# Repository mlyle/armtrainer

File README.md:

# ARM Trainer

This is a minimal monitor and and hardware stack for a small microcontroller trainer board, that was used to teach a Computer Organization class to students from ages 11-14.

Microprocessor trainers were a commonplace tool used to learn computing in the 1970s and early 1980s.  They replicated the console found on minicomputers, and allowed engineers to gain experience writing programs in machine code.

The Computer Organization class that I taught was a "how computers work" class with minimal use of conventional computers in the classroom.  We focused initially on gates, building from there to understand simple combinatorial and sequential circuits, and eventually ALUs, register files, and microprocessor subsystems.  This culminated in a study of ARM-Thumb machine code.

ARM-Thumb machine code was a fairly ideal architecture for students to learn, because:

* It is a real architecture, in real use.
* It has a reasonable number of general purpose registers.
* A fixed-length, relatively simple encoding avoids unnecessary complexity.

## Repository Layout

* `src/` and `inc/` contain the trainer firmware.
* `hw/` contains the KiCad hardware designs and manufacturing outputs.
* `arm-manual/` contains the student manual sources.
* `examples/` contains programs captured from trainers during class.
* `tools/` contains host-side conversion, disassembly, capture, and printing tools.

Run `make tools` to build the host-side utilities in `build/tools/`. The classroom
scripts should be run from any directory; they locate the repository and examples
automatically.

## Example Program

By a student, Robin K:

    20000000	DF20		(clear screen)
    20000002	2001		(mov r0, #1)
    20000004	2102		(mov r1, #1)
    20000006	180A		(add r2, r0, r1)
    20000008	DF21		(print contents of register 0)
    2000000A	4608		(mov r0, r1)
    2000000C	4611		(mov r1, r2)
    2000000E	E7FA		(b 20000006)

## TODO

* Students have complained that some invalid instructions-- BBAD, EF78-- seem to lock up the machine monitor.  I think I removed some safeguard code that I didn't think was necessary, but I need to inspect that again.
* Input calls do not allow the user to enter the number "0".
* The manual should be updated with some of the system calls that have not been documented
  * Branch calculation formulae are wrong in the manual.
  * In particular, the input calls.
  * There may be a typo in the subtract register instruction.
  * The display icon and screen coordinate system could be more clearly explained
  * Need to update manual for new key shortcuts
* Overall curriculum, etc, should get posted here.

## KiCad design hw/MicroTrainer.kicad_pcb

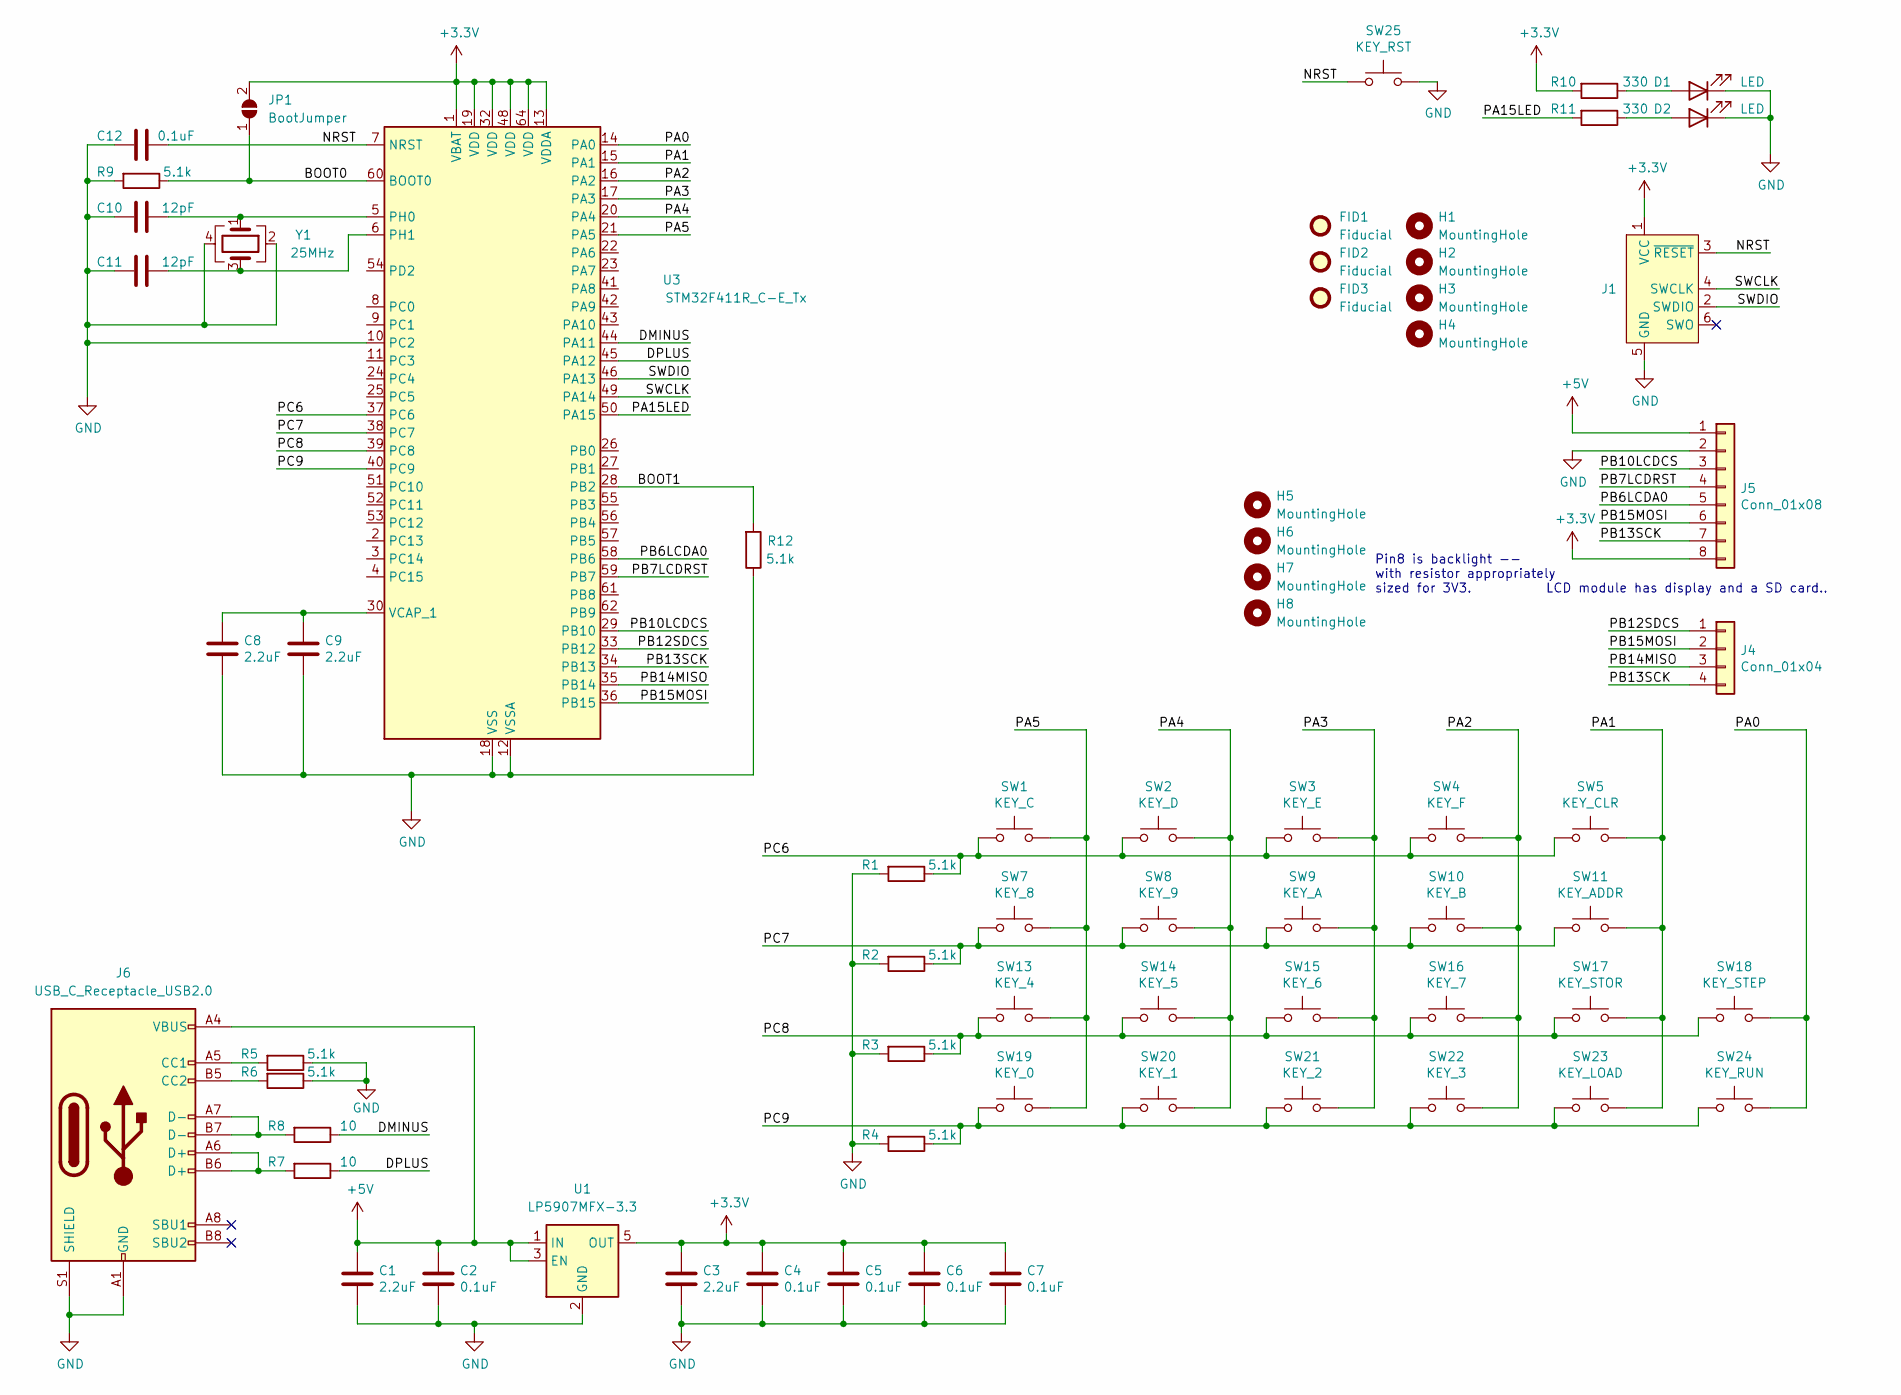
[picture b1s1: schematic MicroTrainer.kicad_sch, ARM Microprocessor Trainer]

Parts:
C1, C3, C8, C9: 2.2uF; C_0603_1608Metric; LCSC C23630
C2, C4, C5, C6, C7, C12: 0.1uF; C_0603_1608Metric; LCSC C14663
C10, C11: 12pF; C_0603_1608Metric; LCSC C38523
D1, D2: LED; LED_0805_2012Metric; LCSC C2297
FID1, FID2, FID3: Fiducial; Fiducial_1mm_Mask2mm
H1, H2, H3, H4, H5, H6, H7, H8: MountingHole; MountingHole_3.2mm_M3
J1: Conn_ARM_SWD_TagConnect_TC2030; Tag-Connect_TC2030-IDC-FP_2x03_P1.27mm_Vertical
J4: Conn_01x04; PinSocket_1x04_P2.54mm_Vertical
J5: Conn_01x08; PinSocket_1x08_P2.54mm_Vertical
J6: USB_C_Receptacle_USB2.0; USB_C_Receptacle_G-Switch_GT-USB-7010ASV; LCSC C2988369
JP1: BootJumper; SolderJumper-2_P1.3mm_Open_RoundedPad1.0x1.5mm
R1, R2, R3, R4, R5, R6, R9, R12: 5.1k; R_0603_1608Metric; LCSC C23186
R7, R8: 10; R_0603_1608Metric; LCSC C22859
R10, R11: 330; R_0603_1608Metric; LCSC C23138
SW1: KEY_C; SW_Cherry_MX_1.00u_PCB
SW2: KEY_D; SW_Cherry_MX_1.00u_PCB
SW3: KEY_E; SW_Cherry_MX_1.00u_PCB
SW4: KEY_F; SW_Cherry_MX_1.00u_PCB
SW5: KEY_CLR; SW_Cherry_MX_1.00u_PCB
SW7: KEY_8; SW_Cherry_MX_1.00u_PCB
SW8: KEY_9; SW_Cherry_MX_1.00u_PCB
SW9: KEY_A; SW_Cherry_MX_1.00u_PCB
SW10: KEY_B; SW_Cherry_MX_1.00u_PCB
SW11: KEY_ADDR; SW_Cherry_MX_1.00u_PCB
SW13: KEY_4; SW_Cherry_MX_1.00u_PCB
SW14: KEY_5; SW_Cherry_MX_1.00u_PCB
SW15: KEY_6; SW_Cherry_MX_1.00u_PCB
SW16: KEY_7; SW_Cherry_MX_1.00u_PCB
SW17: KEY_STOR; SW_Cherry_MX_1.00u_PCB
SW18: KEY_STEP; SW_Cherry_MX_1.00u_PCB
SW19: KEY_0; SW_Cherry_MX_1.00u_PCB
SW20: KEY_1; SW_Cherry_MX_1.00u_PCB
SW21: KEY_2; SW_Cherry_MX_1.00u_PCB
SW22: KEY_3; SW_Cherry_MX_1.00u_PCB
SW23: KEY_LOAD; SW_Cherry_MX_1.00u_PCB
SW24: KEY_RUN; SW_Cherry_MX_1.00u_PCB
SW25: KEY_RST; SW_Cherry_MX_1.00u_PCB
U1: LP5907MFX-3.3; SOT-23-5; LCSC C80670
U3: STM32F411R_C-E_Tx; LQFP-64_10x10mm_P0.5mm; LCSC C89374
Y1: 25MHz; Crystal_SMD_3225-4Pin_3.2x2.5mm; LCSC C9006

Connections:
+3V3: C3.1, C4.1, C5.1, C6.1, C7.1, J1.1 (VCC), J5.8, JP1.2 (B), R10.2, U1.5 (OUT), U3.1 (VBAT), U3.13 (VDDA), U3.19 (VDD), U3.32 (VDD), U3.48 (VDD), U3.64 (VDD)
+5V: C1.1, C2.1, J5.1, J6.A4 (VBUS), J6.A9 (VBUS), J6.B4 (VBUS), J6.B9 (VBUS), U1.1 (IN), U1.3 (EN)
/BOOT0: JP1.1 (A), R9.1, U3.60 (BOOT0)
/BOOT1: R12.2, U3.28 (PB2)
/DMINUS: R8.1, U3.44 (PA11)
/DPLUS: R7.1, U3.45 (PA12)
/NRST: C12.2, J1.3 (~RESET), SW25.1, U3.7 (NRST)
/PA0: SW18.2, SW24.2, U3.14 (PA0)
/PA1: SW5.2, SW11.2, SW17.2, SW23.2, U3.15 (PA1)
/PA2: SW4.2, SW10.2, SW16.2, SW22.2, U3.16 (PA2)
/PA3: SW3.2, SW9.2, SW15.2, SW21.2, U3.17 (PA3)
/PA4: SW2.2, SW8.2, SW14.2, SW20.2, U3.20 (PA4)
/PA5: SW1.2, SW7.2, SW13.2, SW19.2, U3.21 (PA5)
/PA15LED: R11.2, U3.50 (PA15)
/PB6LCDA0: J5.5, U3.58 (PB6)
/PB7LCDRST: J5.4, U3.59 (PB7)
/PB10LCDCS: J5.3, U3.29 (PB10)
/PB12SDCS: J4.1, U3.33 (PB12)
/PB13SCK: J4.4, J5.7, U3.34 (PB13)
/PB14MISO: J4.3, U3.35 (PB14)
/PB15MOSI: J4.2, J5.6, U3.36 (PB15)
/PC6: R1.1, SW1.1, SW2.1, SW3.1, SW4.1, SW5.1, U3.37 (PC6)
/PC7: R2.1, SW7.1, SW8.1, SW9.1, SW10.1, SW11.1, U3.38 (PC7)
/PC8: R3.1, SW13.1, SW14.1, SW15.1, SW16.1, SW17.1, SW18.1, U3.39 (PC8)
/PC9: R4.1, SW19.1, SW20.1, SW21.1, SW22.1, SW23.1, SW24.1, U3.40 (PC9)
/SWCLK: J1.4 (SWCLK), U3.49 (PA14)
/SWDIO: J1.2 (SWDIO), U3.46 (PA13)
GND: C1.2, C2.2, C3.2, C4.2, C5.2, C6.2, C7.2, C8.2, C9.2, C10.1, C11.1, C12.1, D1.1 (K), D2.1 (K), J1.5 (GND), J5.2, J6.A1 (GND), J6.A12 (GND), J6.B1 (GND), J6.B12 (GND), J6.S1 (SHIELD), R1.2, R2.2, R3.2, R4.2, R5.1, R6.1, R9.2, R12.1, SW25.2, U1.2 (GND), U3.10 (PC2), U3.12 (VSSA), U3.18 (VSS), U3.31 (VSS), U3.47 (VSS), U3.63 (VSS), Y1.2, Y1.4
unnamed: D1.2 (A), R10.1
unnamed: D2.2 (A), R11.1
unnamed: J6.A5 (CC1), R5.2
unnamed: J6.B5 (CC2), R6.2
unnamed: J6.A6 (D+), J6.B6 (D+), R7.2
unnamed: J6.A7 (D-), J6.B7 (D-), R8.2
unnamed: C10.2, U3.5 (PH0), Y1.1
unnamed: C11.2, U3.6 (PH1), Y1.3
unnamed: C8.1, C9.1, U3.30 (VCAP_1)

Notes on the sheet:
LCD module has display and a SD card..
Pin8 is backlight -- with resistor appropriately sized for 3V3.

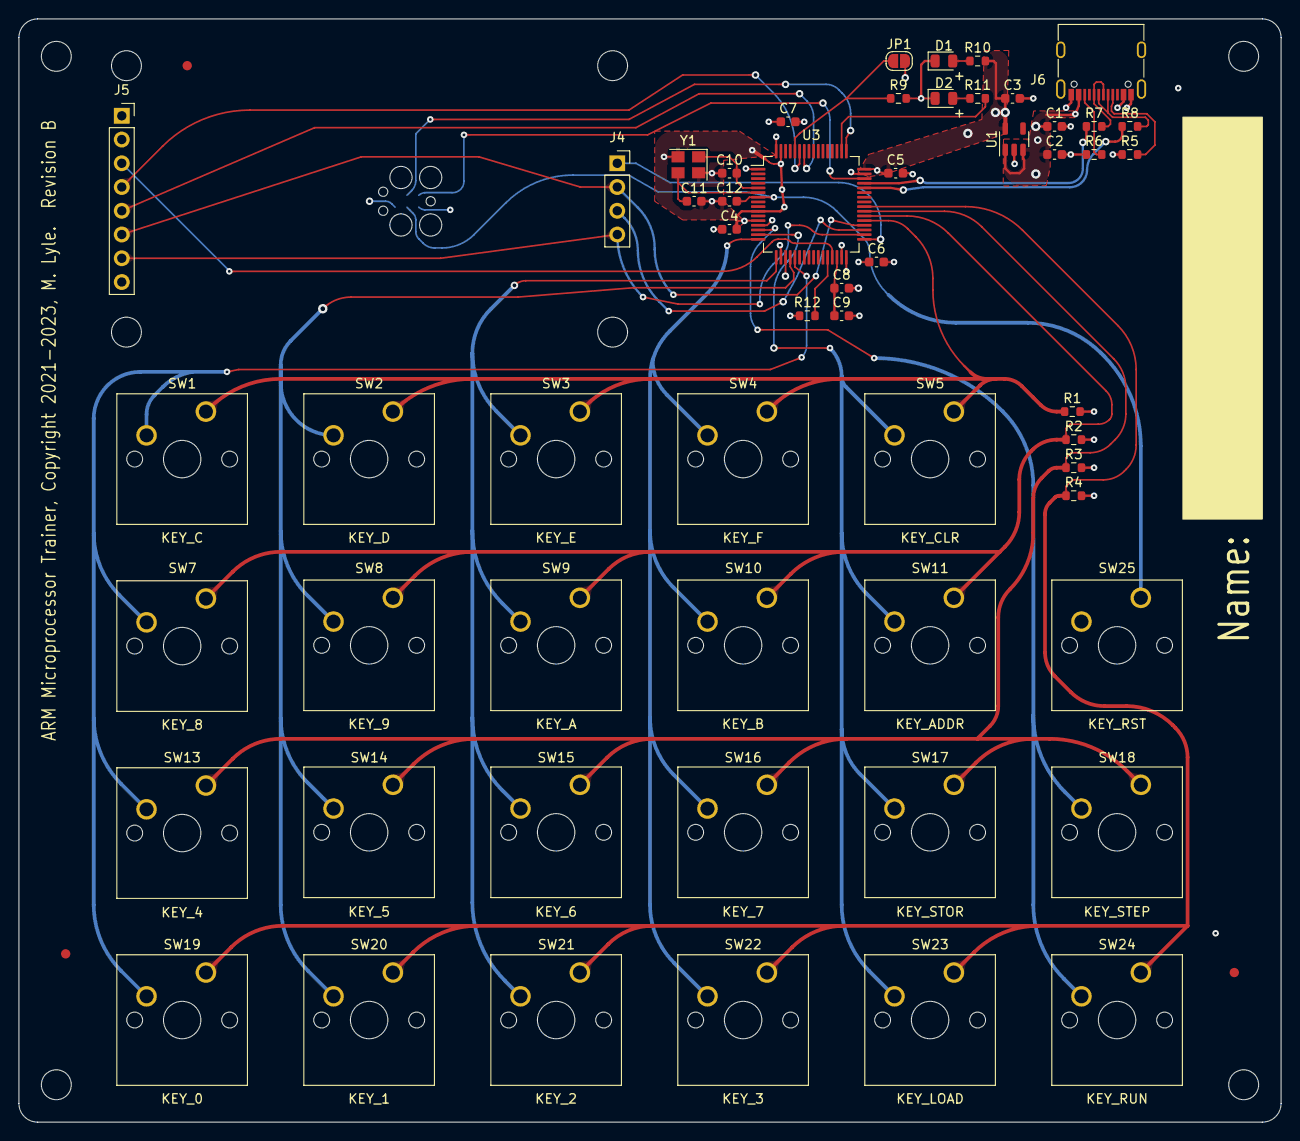
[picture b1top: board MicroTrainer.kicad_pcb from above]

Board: 4 copper layers, 135.0 x 118.0 mm, 68 parts (1 on the bottom side), 37 nets.

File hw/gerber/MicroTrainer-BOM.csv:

Comment,Designator,Footprint,LCSC
"2.2uF","C1,C3,C8,C9","Capacitor_SMD:C_0603_1608Metric","C23630"
"12pF","C10,C11","Capacitor_SMD:C_0603_1608Metric","C38523"
"0.1uF","C2,C4,C5,C6,C7,C12","Capacitor_SMD:C_0603_1608Metric","C14663"
"LED","D1,D2","LED_SMD:LED_0805_2012Metric","C2297"
"Fiducial","FID1,FID2,FID3","Fiducial:Fiducial_1mm_Mask2mm",""
"MountingHole","H1,H2,H3,H4,H5,H6,H7,H8","MountingHole:MountingHole_3.2mm_M3",""
"Conn_01x04","J4","Connector_PinSocket_2.54mm:PinSocket_1x04_P2.54mm_Vertical",""
"Conn_01x08","J5","Connector_PinSocket_2.54mm:PinSocket_1x08_P2.54mm_Vertical",""
"USB_C_Receptacle_USB2.0","J6","Connector_USB:USB_C_Receptacle_G-Switch_GT-USB-7010ASV","C2988369"
"BootJumper","JP1","Jumper:SolderJumper-2_P1.3mm_Open_RoundedPad1.0x1.5mm",""
"5.1k","R1,R2,R3,R4,R5,R6,R9,R12","Resistor_SMD:R_0603_1608Metric","C23186"
"330","R10,R11","Resistor_SMD:R_0603_1608Metric","C23138"
"10","R7,R8","Resistor_SMD:R_0603_1608Metric","C22859"
"KEY_C","SW1","Button_Switch_Keyboard:SW_Cherry_MX_1.00u_PCB",""
"KEY_B","SW10","Button_Switch_Keyboard:SW_Cherry_MX_1.00u_PCB",""
"KEY_ADDR","SW11","Button_Switch_Keyboard:SW_Cherry_MX_1.00u_PCB",""
"KEY_4","SW13","Button_Switch_Keyboard:SW_Cherry_MX_1.00u_PCB",""
"KEY_5","SW14","Button_Switch_Keyboard:SW_Cherry_MX_1.00u_PCB",""
"KEY_6","SW15","Button_Switch_Keyboard:SW_Cherry_MX_1.00u_PCB",""
"KEY_7","SW16","Button_Switch_Keyboard:SW_Cherry_MX_1.00u_PCB",""
"KEY_STOR","SW17","Button_Switch_Keyboard:SW_Cherry_MX_1.00u_PCB",""
"KEY_STEP","SW18","Button_Switch_Keyboard:SW_Cherry_MX_1.00u_PCB",""
"KEY_0","SW19","Button_Switch_Keyboard:SW_Cherry_MX_1.00u_PCB",""
"KEY_D","SW2","Button_Switch_Keyboard:SW_Cherry_MX_1.00u_PCB",""
"KEY_1","SW20","Button_Switch_Keyboard:SW_Cherry_MX_1.00u_PCB",""
"KEY_2","SW21","Button_Switch_Keyboard:SW_Cherry_MX_1.00u_PCB",""
"KEY_3","SW22","Button_Switch_Keyboard:SW_Cherry_MX_1.00u_PCB",""
"KEY_LOAD","SW23","Button_Switch_Keyboard:SW_Cherry_MX_1.00u_PCB",""
"KEY_RUN","SW24","Button_Switch_Keyboard:SW_Cherry_MX_1.00u_PCB",""
"KEY_RST","SW25","Button_Switch_Keyboard:SW_Cherry_MX_1.00u_PCB",""
"KEY_E","SW3","Button_Switch_Keyboard:SW_Cherry_MX_1.00u_PCB",""
"KEY_F","SW4","Button_Switch_Keyboard:SW_Cherry_MX_1.00u_PCB",""
"KEY_CLR","SW5","Button_Switch_Keyboard:SW_Cherry_MX_1.00u_PCB",""
"KEY_8","SW7","Button_Switch_Keyboard:SW_Cherry_MX_1.00u_PCB",""
"KEY_9","SW8","Button_Switch_Keyboard:SW_Cherry_MX_1.00u_PCB",""
"KEY_A","SW9","Button_Switch_Keyboard:SW_Cherry_MX_1.00u_PCB",""
"LP5907MFX-3.3","U1","Package_TO_SOT_SMD:SOT-23-5","C80670"
"STM32F411R_C-E_Tx","U3","Package_QFP:LQFP-64_10x10mm_P0.5mm","C89374"
"25MHz","Y1","Crystal:Crystal_SMD_3225-4Pin_3.2x2.5mm","C9006"

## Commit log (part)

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2021-09-25 Start monitor code base, derived from dRonin OpenLager
    Principal changes in first commit:
    * Adjust for different clocking/part (STM32F401).
    * Run on top of WeAct bootloader (0x8004000 entry) and remove our own loader
    * Adjust memory map to only use top half of memory, leaving bottom half for student programs.
    * Remove usart, sdio, etc, code: can reimport if we need it again
2021-09-26 Massive set of changes
    * Add SVCall handlers for trivial functionality (toggling LEDs, delays)
    * Add sample machine code
    * Bring in DIO and start on keypad scan code
2021-09-26 Complete most of the matrix scanning code
    Change "rows" and "cols" to be inputs and outputs to avoid confusion if
    I decide to drive it the other way. Add code to notice state changes,
    but there's no notification mechanism yet.
2021-09-27 Add SGI 8x13 open source font
    Some small hacks to make it reasonable to use.
    In preparation for LCD work. Various cleanup/refactor still needed.
2021-10-02 Reverse sense of bsrrl/bsrrh.
2021-10-05 Updated test scenario, improved code formatting
2021-10-06 Begin to improve factoring for maintainability
2021-10-06 Get registers on the screen
2021-10-07 Add opcode decode capability
    Improve factoring, etc, somewhat in support of this.
2021-10-07 Add single stepping, and prototpe editing cursor
2021-10-08 add syscall to print number to console
    Also, work towards editing instructions/addresses
2021-10-19 LCD drawing improvements
    - Add utility to blit a single color onto screen
    - Factor internal drawing code separately
    - Add system call (prelim) to blit icon
2021-10-19 AAadd command to setup my build path on windows
2021-10-26 Continued work on monitor & lcd functionality
    - Bounds check LCD draw operations
    - Bounds check character table operations
    - Remove inapplicable comments
    - Move globals closer to the top of monitor.c, add some comments
    - Unify console text drawing functionality, add crude terminal emulation
    - Implement blit dot syscall
2021-10-26 Ensure console is refreshed after outputting a character.
2021-10-29 snake: halt monitored program after game completes
2021-10-30 Improvements to snake game (and related infra)
    - Make everything in stringutil static so it can be imported multiple
    times, and everything inline so we don't get warnings about unused.
    - Adjust memory map; take away 4k of ram from users so that we don't
    stack overflow in snake.
    - Add comment of instruction sequence to invoke snake
    - Make positions a global, so it's easier to analyze ram use.
2021-10-31 Factoring changes and ability to read numbers from console
    - Factor all console routines -- routines relating to the top half of
    the screen -- to console.c.
    - Add new syscalls to read numbers in base 10 and base 16 from console.
    - monitor.c is a much more manageable 581 lines now.
2021-11-02 Add new random number functionality
    - Introduce splitmix64 generator from Sebastiano Vigna.
    - Add crude mechanism allowing blending together multiple seeds
    - Transition snake to this generator
    - Gather entropy data into RNG seed in monitor_key_changed() (keypress
    timing)
    - New system call 0x18: get 32 bit random value.
2021-11-02 Add shortcut to my build environment for flashing
2021-11-02 Improve random number call, console output
    - Correctly handle outputting denary '0'
    - Allow a range to be specified for random numbers (from 0 to r0-1)
2021-11-03 Swap clock phase of SPI going to display module
2021-11-25 Improvements to snake: 4569, erasure, prevent doubling back
2021-11-25 Bring in hardware design
2021-11-25 Add arm manual and source
2021-11-25 Attempt to hide cursor when code is running
2021-11-29 Correct test-for-ram check in debug monitor
2021-11-29 Prevent crashing after attempt to exec invalid addr
2021-11-29 Correct an off-by-one error in snake scaling
    The range of horizontal pixels filled by the LCD driver is from
    startX to endX inclusive, so we need to subtract 1 from the end
    coordinate to scale properly.
2021-11-29 Capture example program and todo in README
2021-11-29 Readme: Add mptrainer image
2021-12-01 Add errata/todo
2023-12-17 Staging in preparation of review and ordering
2023-12-17 add cherry switch 3d step model
2023-12-17 Remove errata.
2023-12-17 MicroTrainer Rev B
2023-12-18 Update to reflect we're using STM32F412
2023-12-18 Update source for rev b-- changed gpio assignments
2023-12-18 Adjust LCD driver to use DMA.
2023-12-19 Move stack to top of all ram
2023-12-19 snake: move position list to stack
2023-12-19 reindent snake.c
2023-12-19 Add support for transparent icon blit syscall
2023-12-19 blit_registers: support showing high registers
2023-12-19 improve indenting
2023-12-19 Update copyright message
2023-12-19 add const qualifier to string in lcd_blit_string
2023-12-28 Toggle auxiliary LED every 1024 keyboard scans
    For bringup, but it's not a bad troubleshooting thing in general.
2023-12-29 Fix key mapping -- rows were reversed
2023-12-29 Correct LCD DMA implementation
2023-12-30 Adjust snake to leave trace of a grid behind
2023-12-30 Correct clock rate comments, document more
2023-12-30 Mostly documentation changes to console
2023-12-30 Plumb functionality for 'load' as modifier key
    When 'load' is held, other keys have special meaning.
    0-3 select different "register screens'.
    f toggles "fast mode".
2023-12-30 Update HSE_VALUE to be correct value in Makefile
    25MHz, not 8MHz
2023-12-30 Add hyperref to manual
2023-12-30 Add 4x11 font
2023-12-30 add lcd_blit_box routine
2023-12-30 snake: use lcd_blit_box
2023-12-30 Add hex digits to font 4x11.
2023-12-30 Add support for 4x11 font to lcd routines
2023-12-30 When blitting registers, ensure intervening areas are blank
2023-12-30 Attempt to improve use of load as a modifier
    Only perform load action on release of key
    Don't perform load action if was used as modifier
    Don't refresh screen in the matrix callback; rely upon code to now
    be consistently refreshing
2023-12-30 Add implementation of disassembly of surrounding insn
2023-12-30 Add in back "really fast" mode (undoc'd)
2023-12-30 add new "decimal display mode" for registers
    Also constify stringutil functions returning internal buffers
2023-12-30 const-ify the font bitmaps so they are kept in flash
    And not copied to ram in data segment
2024-01-01 Corrections to make instruction view work
    - Add spaces before immediates
    - use proper color values
    - fix edge cases with numbers in small font
2024-01-01 Small corrections to screen blitting for decimals, etc
2024-01-01 Lots of additional documentation
2024-01-01 Moved all files in shared dir to src
    This is legacy from a prior project where there were "shared" files
    used by a bootloader.
    This has pretty definitively moved to using the STM32 system loader
    for flashing, so that won't be used here. Therefore, let's simplify
    the path hierarchy.
2024-01-01 License details nad documentation of 4x11 font.
2024-01-01 Disable keyboard matrix LED
    It was useful for bringup, but now let's free up the LED for
    students.
2024-01-01 Move thumb disassembly into separate header lib
2024-01-01 Adjust systick rate to be in a define
2024-01-01 lcd: Don't enable display until first frame blitted
    This slightly speeds up startup and avoids an annoying black flash.
2024-01-01 Various startup changes to monitor.c
    - Factor hardware-specific clock programming to separate function.
    - Initialize and check matrix earlier in startup
    - Display "going to loader" when entering bootloader
2024-01-01 Center "going to loader" on screen
2024-01-02 Improvements to disassembling
    - Output hex instruction correctly
    - More clearly highlight current instruction
2024-01-02 Update manual-- pdf bookmarks
    Likely to have a rather massive revision soon. But this is a
    worthwhile change first.
2024-01-03 Attempt to drive 30MHz clock out PA6
    (pin 22).
    This is for diagnostic purposes only, but the fraction of a milliampere
    that this uses is irrelevant, so always enable it.
2024-01-04 Correct small typeface display of 7 & 9
2024-01-12 add LCD_Release call for future use.
2024-01-30 update image of mptrainer for revB hw.
2024-01-30 Note that keys need debouncing
2024-02-13 Debounce keys in software.
2024-02-15 Add routine to write strings to console
2024-02-15 Add new save subsystem
2024-02-15 Improve output of save/load messages
2024-02-15 make save slot 2 work
2024-02-28 Make decoding of next instruction slightly more obvious
2024-04-25 Update arm manual with revisions for 2024
2024-05-04 Update README to match current state of manual, etc.
2024-05-09 Update manual errata
2024-05-17 Update README with future enhancements and errata
2024-05-19 add SVC1A: determine last key pressed during run
    This will make writing games, etc, more practical.
2024-05-19 Add SVC19: returns time since startup in ms
2024-05-19 Clear flash flags
    Students experiences problems saving-- probably because they had tried
    to write to flash accidentally. Let's make sure before attempting to
    save that all error flags are cleared.
2024-05-19 Disassemble 0000 as NOP, not LSLi
2024-05-19 Add branch calculator function
    Students have a hard time calculating branches-- especially since they
    are all backwards and I just barely teach the students 2's complement
    notation. So now I have added a branch calculator to the monitor code
    that will hopefully help.
2024-05-19 Add break missing from switch statement
2024-05-19 add alternate way to get to snake easter egg
    Now typing 08028616 into the address bar and hitting ADDR suffices.
2024-05-19 improve branch calculator and fix some bugs
    While this is still as-yet untested, I noticed that the subtraction
    was in the incorrect order (was start - target instead of the
    opposite) and that I had failed to account for the way the
    instruction pointer is already incremented at the time of the
    branch.
    While we're at it, let's make sure the source address is valid,
2024-05-19 Improve readme list of todo tasks
    Mostly the only stuff to do remaining is:
    - Get curriculum online
    - Rev manual once more
    - Validate handling of invalid instructions
2024-05-20 console: accept 'step' as the end of the number
    (But what we really want to do is force user to use store/load to
    end, and let a program be stopped using the step/run keys).
2024-05-20 note that we need the new key shortcuts in the manual
2024-05-20 branch helper: don't let our idea of 'load' get stuck
    Because we go to a different keyboard helper when reading input,
    the release of the 'load' key was getting lost by the main monitor,
    which was confounding all subsequent efforts to interact.
2024-05-20 Correct branch in snake example to go back to begin
2024-05-21 Correct help -- hold "LOAD" not "ADDR"

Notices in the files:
hw/MicroTrainer.kicad_pcb:
ARM Microprocessor Trainer, Copyright 2021-2023, M. Lyle.  Revision B
